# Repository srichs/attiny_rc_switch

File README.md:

# ATtiny RC Switch

On/Off Switch for RC models driven by PWM signal. Based on ATtiny85, 12V capable. Original project is located [here](https://github.com/DzikuVx/attiny_rc_switch).

This small device allows to turn on/off different devices on RC devices: airplanes, quadcopter drones, cars. 
It uses one RC PWM channel as input and provides power on output pins when channel pulse length is above 1700us.
Excellent to switch LED strips. Output current is up to 500mA.

AVR ATtiny x5 series microcontroller. Compiled code takes slightly above 2kB, so will fit into ATtiny45 and ATtiny85. When smoothing is removed, code will fit into ATtiny25.

To program you can use the [AVR Pocket Programmer](https://www.digikey.com/en/products/detail/sparkfun-electronics/09825/5230949), which costs $20. It is easiest to use a clip to program the microcontroller such as [these](https://www.amazon.com/EC-Buying-Detachable-Programmer-Testing/dp/B0C73GXRR2) or [these](https://www.amazon.com/Programmer-Testing-SOP16-SOIC8-SOIC16/dp/B0CBNG59CB).

## ATtiny RC Switch SMD

Order the PCB [here](https://oshpark.com/shared_projects/qRILFycT)

## Hardware

### BOM

| Label |Part No    | Name     | Quantity | Subtotal | Link   |
|-------|-----------|----------|----------|----------|--------|
| U1 | ATTINY85-20SU | ATtiny85 Microcontroller | 1 | $1.50 | [DigiKey](https://www.digikey.com/en/products/detail/microchip-technology/ATTINY85-20SU/735470) |
| U2 | IRLML2502TRPBF | N-Channel MOSFET, 20V, 4.2A SOT-23 | 1 | $0.43 | [DigiKey](https://www.digikey.com/en/products/detail/infineon-technologies/IRLML2502TRPBF/812502) |
| D1 | LTST-C190KRKT | Red LED, SMD 0603, Clear | 1 | $0.14 | [DigiKey](https://www.digikey.com/en/products/detail/liteon/LTST-C190KRKT/386817) |
| R1,R2 | CRGCQ0603F470R | 470 Ohm Resistor, SMD 0603, 1/10W | 2 | $0.20 | [DigiKey](https://www.digikey.com/en/products/detail/te-connectivity-passive-product/CRGCQ0603F470R/8576286) |
| C1 | CC0603KRX7R7BB104 | 0.1uF Capacitor, SMD 0603, 16V | 1 | $0.08 | [DigiKey](https://www.digikey.com/en/products/detail/yageo/CC0603KRX7R7BB104/302822) |
|  | qRILFycT | PCB | 1 | $0.68 | [OSH Park](https://oshpark.com/shared_projects/qRILFycT) |
|  |  |  | Total | $3.03 |  |

### Schematic

## ATtiny RC Switch Through Hole

Order the PCB [here](https://oshpark.com/)

## Hardware

### BOM

| Label |Part No    | Name     | Quantity | Subtotal | Link   |
|-------|-----------|----------|----------|----------|--------|
| U1 | ATTINY85-20PU | ATtiny85 Microcontroller | 1 | $1.66 | [DigiKey](https://www.digikey.com/en/products/detail/microchip-technology/ATTINY85-20PU/735469?s=N4IgTCBcDaIIYBcEEsB2BPAHAVgLRgAYAHAVxAF0BfIA) |
| U2 | SS8050DTA | NPN BJT, 25V, 1.5A TO92-3 | 1 | $0.37 | [DigiKey](https://www.digikey.com/en/products/detail/onsemi/SS8050DTA/1047325) |
| D1 | 151033RS03000 | Red LED, Round, 3mm, Clear | 1 | $0.16 | [DigiKey](https://www.digikey.com/en/products/detail/w%C3%BCrth-elektronik/151033RS03000/4490003) |
| R1,R2 | CF18JT470R | 470 Ohm Resistor, 1/8W, Axial | 2 | $0.20 | [DigiKey](https://www.digikey.com/en/products/detail/stackpole-electronics-inc/CF18JT470R/1741717) |
| C1 | A104K15X7RF5TAA | 0.1uF Capacitor, 50V, Axial | 1 | $0.26 | [DigiKey](https://www.digikey.com/en/products/detail/vishay-beyschlag-draloric-bc-components/A104K15X7RF5TAA/146011) |
|  |  |  | Total | $2.65 |  |

### Schematic

## Notes

* Arduino IDE 1.6.6. Should work on older releases, but never tested

* ATtiny45/85 board definitions. Tested with [damellis/attiny](https://github.com/damellis/attiny)

* Uses 1MHz internal osciallator

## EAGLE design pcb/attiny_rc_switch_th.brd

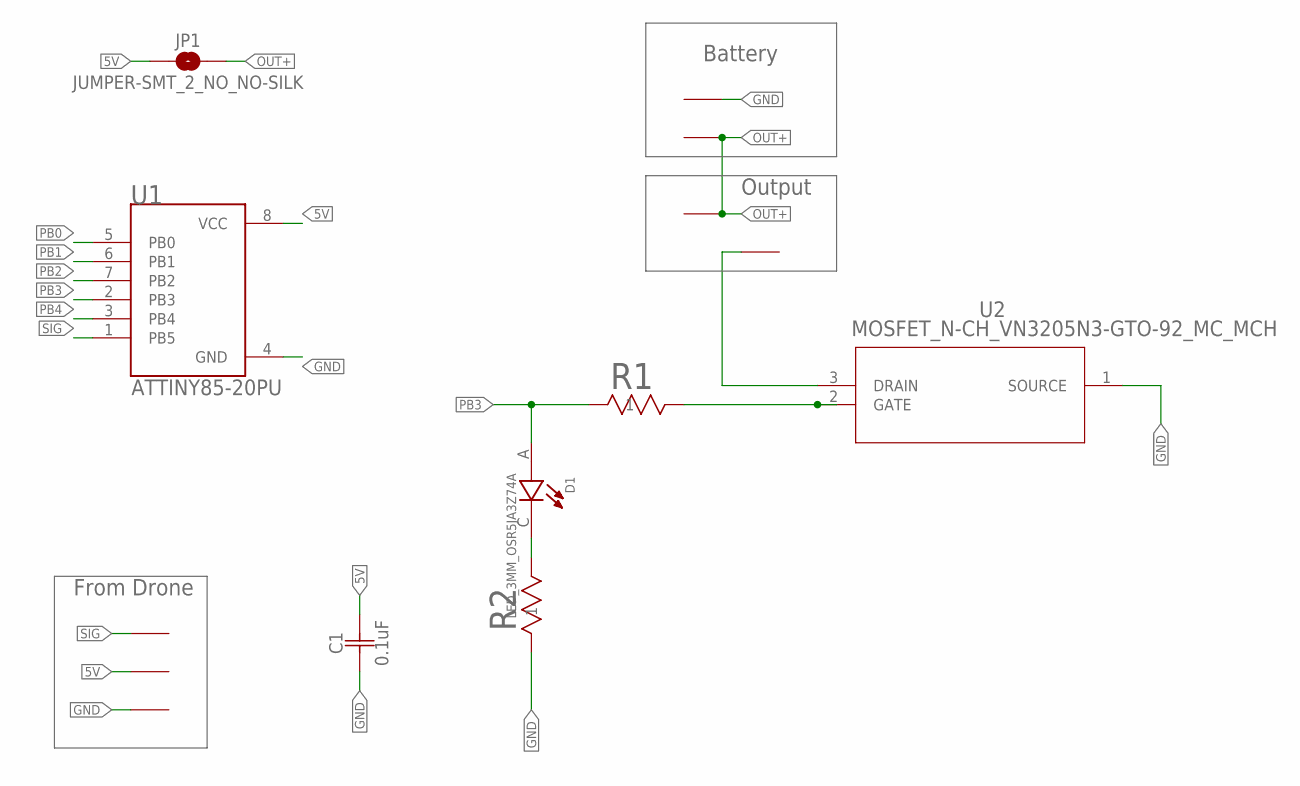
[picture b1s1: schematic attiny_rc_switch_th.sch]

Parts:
C1: 0.1uF; K10XK10X7RF5UH5
D1: LED_3MM_OSR5JA3Z74A; OSR5JA3Z74A
JP1: JUMPER-SMT_2_NO_NO-SILK; SMT-JUMPER_2_NO_NO-SILK
R1, R2: RESISTOR_1/8W_CF18JTSTA_CF18_STP; RESISTOR_1/8W_CF18JT
U1: ATTINY85-20PU
U2: MOSFET_N-CH_VN3205N3-GTO-92_MC_MCH; MOSFET_N-CH_VN3205N3-G
U$1, U$2, U$3, U$4, U$5, U$6, U$8: SMD_PAD

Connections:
5V: C1.2, JP1.1, U1.8 (VCC), U$1.P$1
GND: C1.1, R2.1, U1.4 (GND), U2.1 (SOURCE), U$2.P$1, U$4.P$1
unnamed: R1.2, U2.2 (GATE)
unnamed: D1.C, R2.2
OUT+: JP1.2, U$3.P$1, U$5.P$1
OUT-: U2.3 (DRAIN), U$6.P$1
PB0: U1.5 (PB0)
PB1: U1.6 (PB1)
PB2: U1.7 (PB2)
PB3: D1.A, R1.1, U1.2 (PB3)
PB4: U1.3 (PB4)
SIG: U1.1 (PB5), U$8.P$1

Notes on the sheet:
From Drone
Battery
Output

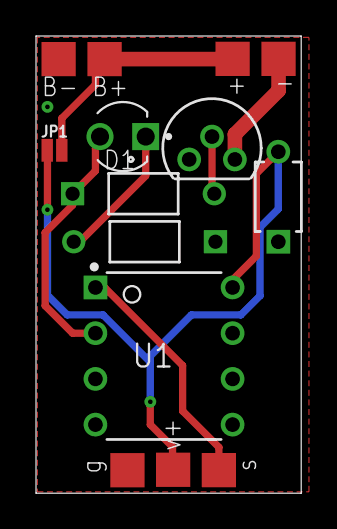
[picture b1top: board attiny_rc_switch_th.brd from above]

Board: 2 copper layers, 14.7 x 25.4 mm, 14 parts (0 on the bottom side), 8 nets.

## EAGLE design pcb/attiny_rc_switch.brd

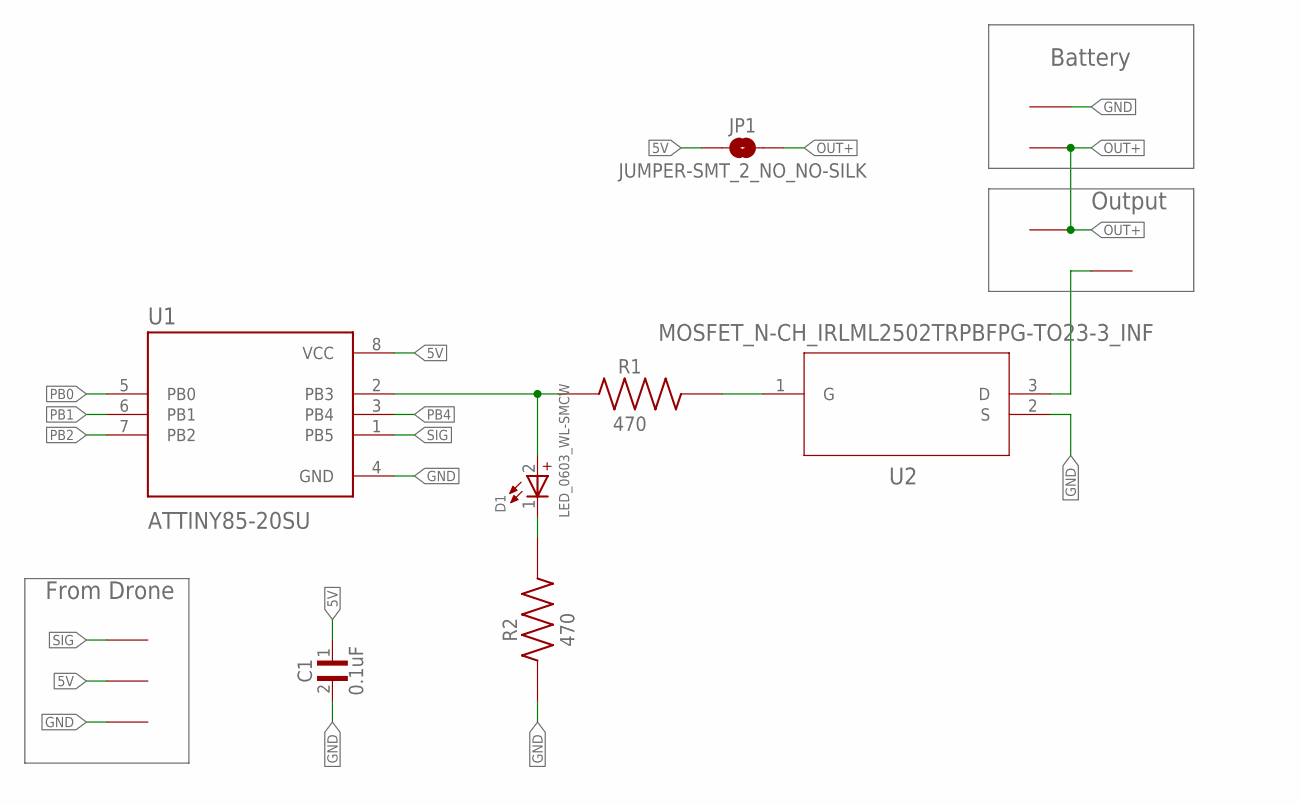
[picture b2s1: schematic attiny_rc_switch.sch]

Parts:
C1: 0.1uF; CC0603ZRY5V9BB
D1: LED_0603_WL-SMCW
JP1: JUMPER-SMT_2_NO_NO-SILK; SMT-JUMPER_2_NO_NO-SILK
R1, R2: 470; RCS0603
U1: ATTINY85-20SU
U2: MOSFET_N-CH_IRLML2502TRPBFPG-TO23-3_INF; MOSFET_N-CH_IRLML2502TRPBF
U$1, U$2, U$3, U$4, U$5, U$6, U$8: SMD_PAD

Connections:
5V: C1.1, JP1.1, U1.8 (VCC), U$1.P$1
GND: C1.2, R2.1, U1.4 (GND), U2.2 (S), U$2.P$1, U$4.P$1
unnamed: D1.2 (+), R1.1, U1.2 (PB3)
unnamed: R1.2, U2.1 (G)
unnamed: D1.1 (-), R2.2
OUT+: JP1.2, U$3.P$1, U$5.P$1
OUT-: U2.3 (D), U$6.P$1
PB0: U1.5 (PB0)
PB1: U1.6 (PB1)
PB2: U1.7 (PB2)
PB4: U1.3 (PB4)
SIG: U1.1 (PB5), U$8.P$1

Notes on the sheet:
From Drone
Battery
Output

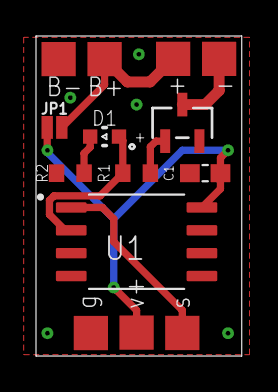
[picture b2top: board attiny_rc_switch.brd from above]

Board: 2 copper layers, 11.4 x 17.8 mm, 14 parts (0 on the bottom side), 8 nets.

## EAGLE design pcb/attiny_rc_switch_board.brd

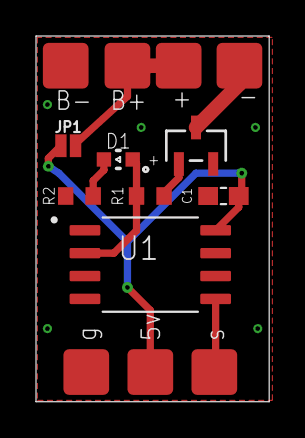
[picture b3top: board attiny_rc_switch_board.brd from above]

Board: 2 copper layers, 13.0 x 20.3 mm, 14 parts (0 on the bottom side), 8 nets.

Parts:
C1: 0.1uF; CC0603ZRY5V9BB
D1: LED_0603_WL-SMCW
JP1: JUMPER-SMT_2_NO_NO-SILK; SMT-JUMPER_2_NO_NO-SILK
R1, R2: 470; RCS0603
U1: ATTINY85-20SU
U2: MOSFET_N-CH_IRLML2502TRPBFPG-TO23-3_INF; MOSFET_N-CH_IRLML2502TRPBF
U$1, U$2, U$3, U$4, U$5, U$6, U$7: SMD_PAD_NO_STENCIL

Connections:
5V: C1.1, JP1.1, U1.8, U$2.P$1
GND: C1.2, R2.1, U1.4, U2.2, U$6.P$1, U$7.P$1
unnamed: D1.2, R1.1, U1.2
unnamed: R1.2, U2.1
unnamed: D1.1, R2.2
OUT+: JP1.2, U$4.P$1, U$5.P$1
OUT-: U2.3, U$3.P$1
SIG: U1.5, U$1.P$1

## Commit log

2016-01-06 code
2016-01-07 electrical improvements
2016-01-31 README update
2025-05-18 added pcb, changed code & readme
2025-05-18 added pcb files
2025-05-20 added through hole pcb
2025-05-22 remove unused variable; fix definitions
2025-05-31 fixed signal pin, changed pads
2025-05-31 minor code fixes
2025-05-31 update pcb order link
2025-05-31 added pcb to BOM
2025-06-10 fixed output pads
2025-06-10 fixed readme

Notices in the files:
parts and their libraries:
SparkFun-Jumpers: Licensing: Creative Commons ShareAlike 4.0 International - https://creativecommons.org/licenses/by-sa/4.0
COPYRIGHT: Copyright (C) 2024 Ultra Librarian. All rights reserved.
COPYRIGHT: Copyright (C) 2025 Ultra Librarian. All rights reserved.
